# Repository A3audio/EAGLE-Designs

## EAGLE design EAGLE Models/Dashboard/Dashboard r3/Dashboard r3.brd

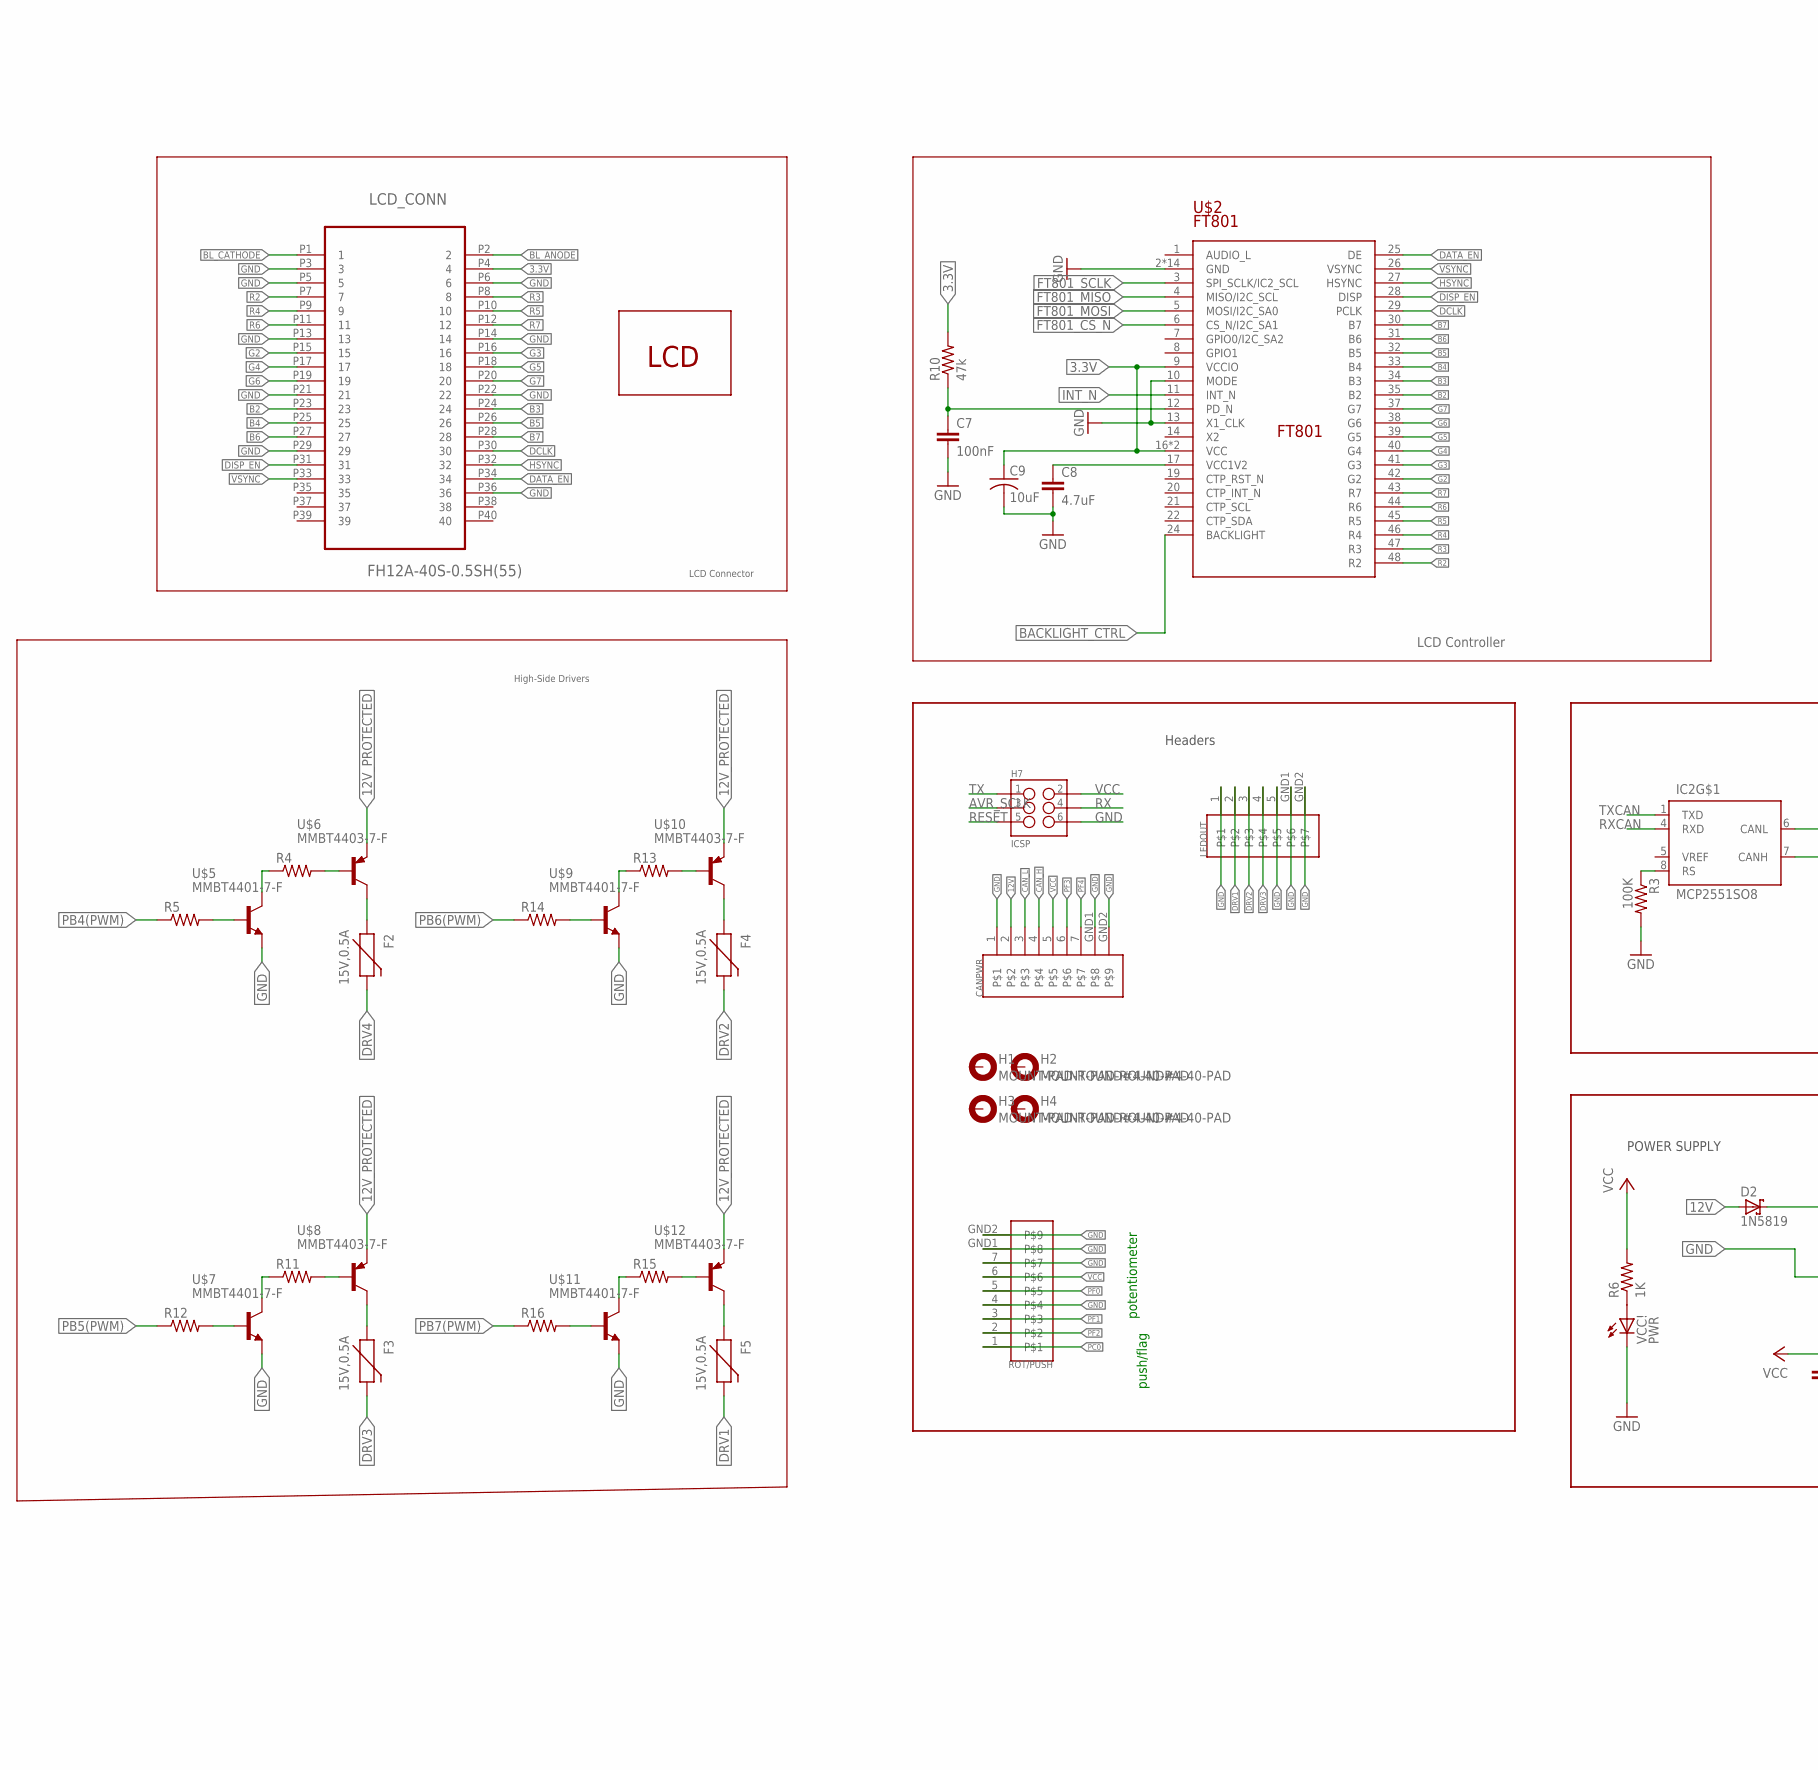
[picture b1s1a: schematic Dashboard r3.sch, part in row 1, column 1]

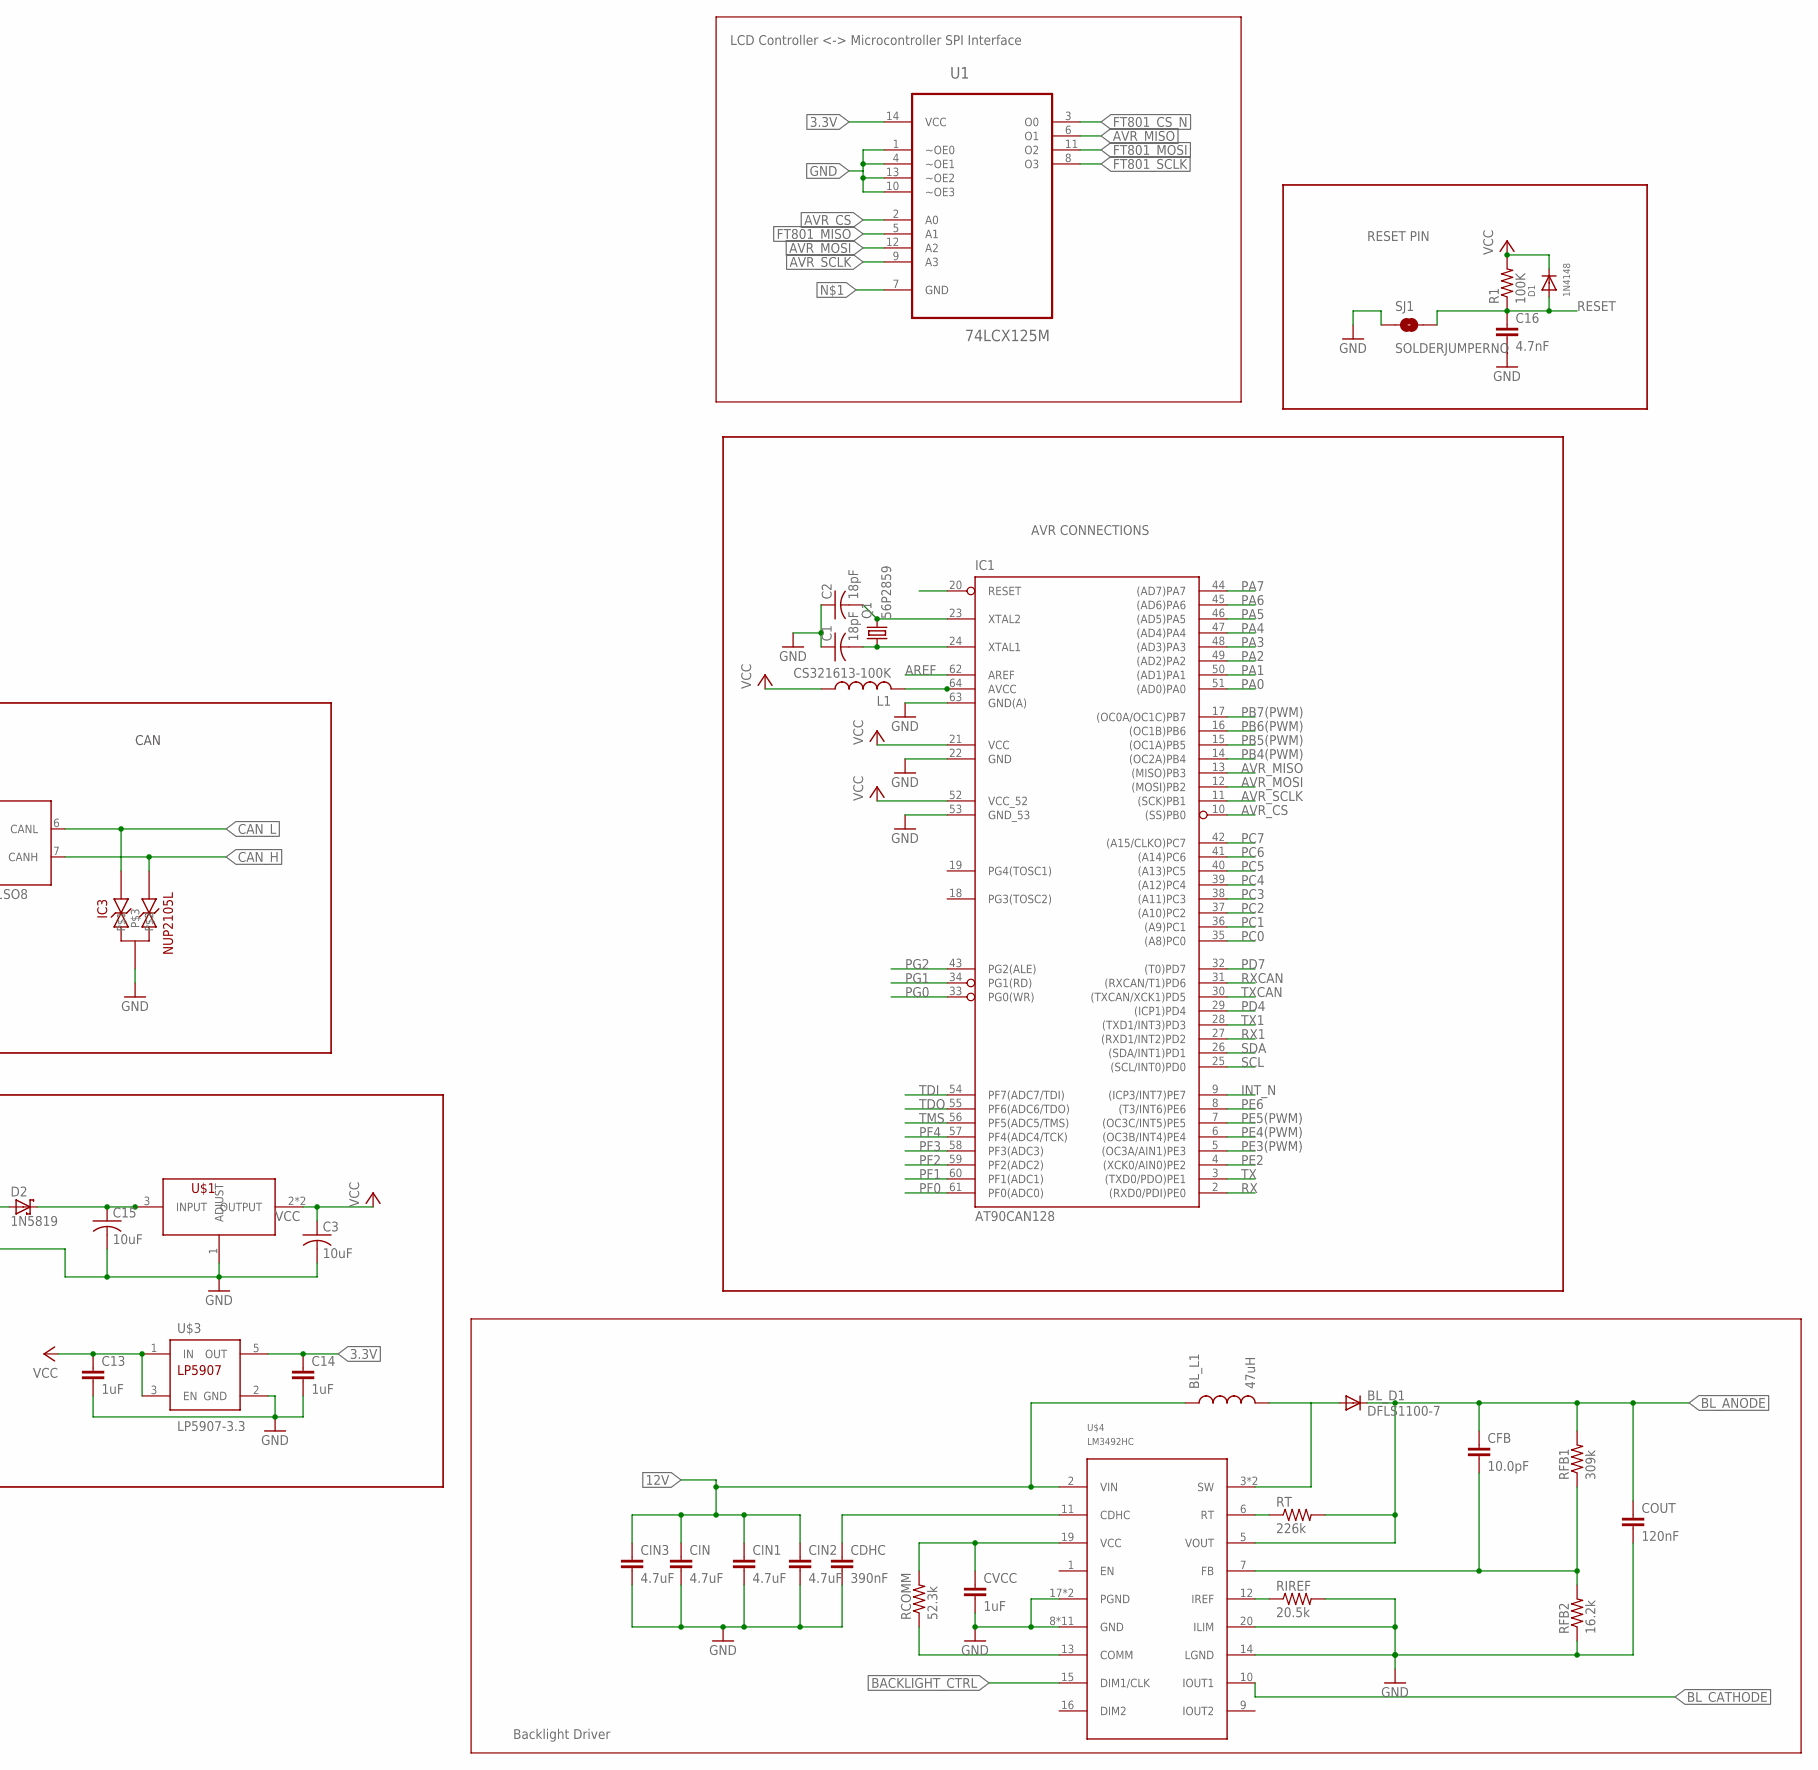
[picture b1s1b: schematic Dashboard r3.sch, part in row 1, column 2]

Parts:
BL_D1: DFLS1100-7; POWERDI-123
BL_L1: 47uH; 2-SMD
C1, C2: 18pF; C0805
C3, C9, C15: 10uF; C2220
C7: 100nF; 0603-CAP
C8: 4.7uF; 0805
C13, C14: 1uF; 0603-CAP
C16: 4.7nF; 0805
CANPWR: 53261-0771
CDHC: 390nF; 0603-CAP
CFB: 10.0pF; 0603-CAP
CIN, CIN1, CIN2, CIN3: 4.7uF; 0805
COUT: 120nF; 0805
CVCC: 1uF; 0603-CAP
D1: 1N4148; SOD-123
D2: 1N5819; SOD123
F2, F3, F4, F5: 15V,0.5A; PTC-1206
H1, H2, H3, H4: MOUNT-PAD-ROUND#4-40-PAD; #4-40-PAD-ROUND
H7: ICSP; 2X3_SMD_FCI_54202-G30
IC1: AT90CAN128; TQFP64
IC2: MCP2551SO8; SO08
IC3: NUP2105L; SOT-23
L1: CS321613-100K; L3216C
LCD_CONN: FH12A-40S-0.5SH(55); HIROSE_FH12A-40S-0.5SH(55)
LEDOUT: 53261-0571
Q1: 56P2859; HC49UP
R1, R3: 100K; R0805
R4, R5, R11, R12, R13, R14, R15, R16: RESISTOR0603; 0603-RES
R6: 1K; R0805
R10: 47k; 0603-RES
RCOMM: 52.3k; 0603-RES
RFB1: 309k; 0603-RES
RFB2: 16.2k; 0603-RES
RIREF: 20.5k; 0603-RES
ROT/PUSH: 53261-0771
RT: 226k; 0603-RES
SJ1: SOLDERJUMPERNO; SJ_2S-NO
U1: 74LCX125M; SOIC127P600X175-14N
U$1: NCP1117; SOT-223-4
U$2: FT801; RGZ48_5P15X5P15
U$3: LP5907-3.3; SOT23-DBV
U$4: LM3492HC; PWP0020A
U$5, U$7, U$9, U$11: MMBT4401-7-F; SOT-23-3
U$6, U$8, U$10, U$12: MMBT4403-7-F; SOT-23-3
U$13: TCG043WQLBAANN-GN00; TCG043WQLBAANN
VCC!: PWR; CHIPLED_0805

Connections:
3.3V: C9.1, C14.1, LCD_CONN.P4 (4), R10.2, U1.14 (VCC), U$2.9 (VCCIO), U$2.16 (VCC), U$2.18 (VCC), U$3.5 (OUT)
12V: BL_L1.1, CANPWR.2, CIN.1, CIN1.1, CIN2.1, CIN3.1, D2.A, U$4.2 (VIN)
12V_PROTECTED: C15.1, D2.C, U$1.3 (INPUT), U$6.P$3 (E), U$8.P$3 (E), U$10.P$3 (E), U$12.P$3 (E)
AREF: IC1.62 (AREF)
AVR_CS: IC1.10 ((SS)PB0), U1.2 (A0)
AVR_MISO: IC1.13 ((MISO)PB3), U1.6 (O1)
AVR_MOSI: IC1.12 ((MOSI)PB2), U1.12 (A2)
AVR_SCLK: H7.3, IC1.11 ((SCK)PB1), U1.9 (A3)
B2: LCD_CONN.P23 (23), U$2.35 (B2)
B3: LCD_CONN.P24 (24), U$2.34 (B3)
B4: LCD_CONN.P25 (25), U$2.33 (B4)
B5: LCD_CONN.P26 (26), U$2.32 (B5)
B6: LCD_CONN.P27 (27), U$2.31 (B6)
B7: LCD_CONN.P28 (28), U$2.30 (B7)
BACKLIGHT_CTRL: U$2.24 (BACKLIGHT), U$4.15 (DIM1/CLK)
BL_ANODE: BL_D1.C, CFB.1, COUT.1, LCD_CONN.P2 (2), RFB1.2, RT.2, U$4.5 (VOUT)
BL_CATHODE: LCD_CONN.P1 (1), U$4.10 (IOUT1)
CAN_H: CANPWR.4, IC2.7 (CANH), IC3.2
CAN_L: CANPWR.3, IC2.6 (CANL), IC3.1
DATA_EN: LCD_CONN.P34 (34), U$2.25 (DE)
DCLK: LCD_CONN.P30 (30), U$2.29 (PCLK)
DISP_EN: LCD_CONN.P31 (31), U$2.28 (DISP)
DRV1: F5.2, LEDOUT.2
DRV2: F4.2, LEDOUT.3
DRV3: F3.2, LEDOUT.4
DRV4: F2.2
FT801_CS_N: U1.3 (O0), U$2.6 (CS_N/I2C_SA1)
FT801_MISO: U1.5 (A1), U$2.4 (MISO/I2C_SCL)
FT801_MOSI: U1.11 (O2), U$2.5 (MOSI/I2C_SA0)
FT801_SCLK: U1.8 (O3), U$2.3 (SPI_SCLK/IC2_SCL)
G2: LCD_CONN.P15 (15), U$2.42 (G2)
G3: LCD_CONN.P16 (16), U$2.41 (G3)
G4: LCD_CONN.P17 (17), U$2.40 (G4)
G5: LCD_CONN.P18 (18), U$2.39 (G5)
G6: LCD_CONN.P19 (19), U$2.38 (G6)
G7: LCD_CONN.P20 (20), U$2.37 (G7)
GND: C1.1, C2.1, C3.2, C7.2, C8.2, C9.2, C13.2, C14.2, C15.2, C16.2, CANPWR.1, CDHC.2, CIN.2, CIN1.2, CIN2.2, CIN3.2, COUT.2, CVCC.2, H7.6, IC1.22 (GND), IC1.53 (GND_53), IC1.63 (GND(A)), IC2.2 (GND), IC3.3, LCD_CONN.P3 (3), LCD_CONN.P5 (5), LCD_CONN.P6 (6), LCD_CONN.P13 (13), LCD_CONN.P14 (14), LCD_CONN.P21 (21), LCD_CONN.P22 (22), LCD_CONN.P29 (29), LCD_CONN.P36 (36), LEDOUT.1, LEDOUT.5, LEDOUT.GND1, LEDOUT.GND2, R3.2, RFB2.1, RIREF.2, ROT/PUSH.4, ROT/PUSH.7, ROT/PUSH.GND1, ROT/PUSH.GND2, SJ1.1, U1.1 (~OE0), U1.4 (~OE1), U1.10 (~OE3), U1.13 (~OE2), U$1.1 (ADJUST), U$2.2 (GND), U$2.10 (MODE), U$2.13 (X1_CLK), U$2.15 (GND), U$2.23 (GND), U$2.36 (GND), U$2.EP (GND), U$2.V_1 (GND), U$2.V_2 (GND), U$2.V_3 (GND), U$2.V_4 (GND), U$2.V_5 (GND), U$2.V_6 (GND), U$2.V_7 (GND), U$2.V_8 (GND), U$2.V_9 (GND), U$3.2 (GND), U$4.8 (GND), U$4.14 (LGND), U$4.17 (PGND), U$4.18 (PGND), U$4.20 (ILIM), U$4.EP (GND), U$4.P$1 (GND), U$4.P$2 (GND), U$4.P$3 (GND), U$4.P$4 (GND), U$4.P$5 (GND), U$4.P$6 (GND), U$4.P$7 (GND), U$4.P$8 (GND), U$4.P$9 (GND), U$5.P$3 (E), U$7.P$3 (E), U$9.P$3 (E), U$11.P$3 (E), VCC!.C
HSYNC: LCD_CONN.P32 (32), U$2.27 (HSYNC)
INT_N: IC1.9 ((ICP3/INT7)PE7), U$2.11 (INT_N)
unnamed: C8.1, U$2.17 (VCC1V2)
unnamed: C7.1, R10.1, U$2.12 (PD_N)
unnamed: CVCC.1, RCOMM.2, U$4.19 (VCC)
unnamed: RCOMM.1, U$4.13 (COMM)
unnamed: IC2.8 (RS), R3.1
unnamed: CDHC.1, U$4.11 (CDHC)
unnamed: BL_D1.A, BL_L1.2, U$4.3 (SW), U$4.4 (SW)
unnamed: R6.1, VCC!.A
unnamed: CFB.2, RFB1.1, RFB2.2, U$4.7 (FB)
unnamed: C1.2, IC1.24 (XTAL1), Q1.1
unnamed: RT.1, U$4.6 (RT)
unnamed: RIREF.1, U$4.12 (IREF)
unnamed: IC1.64 (AVCC), L1.2
unnamed: R5.2, U$5.P$2 (B)
unnamed: R4.2, U$6.P$2 (B)
unnamed: R4.1, U$5.P$1 (C)
unnamed: F2.1, U$6.P$1 (C)
unnamed: R12.2, U$7.P$2 (B)
unnamed: R11.2, U$8.P$2 (B)
unnamed: R11.1, U$7.P$1 (C)
unnamed: F3.1, U$8.P$1 (C)
unnamed: R14.2, U$9.P$2 (B)
unnamed: R13.2, U$10.P$2 (B)
unnamed: R13.1, U$9.P$1 (C)
unnamed: F4.1, U$10.P$1 (C)
unnamed: R16.2, U$11.P$2 (B)
unnamed: R15.2, U$12.P$2 (B)
unnamed: R15.1, U$11.P$1 (C)
unnamed: F5.1, U$12.P$1 (C)
PA0: IC1.51 ((AD0)PA0)
PA1: IC1.50 ((AD1)PA1)
PA2: IC1.49 ((AD2)PA2)
PA3: IC1.48 ((AD3)PA3)
PA4: IC1.47 ((AD4)PA4)
PA5: IC1.46 ((AD5)PA5)
PA6: IC1.45 ((AD6)PA6)
PA7: IC1.44 ((AD7)PA7)
PB4(PWM): IC1.14 ((OC2A)PB4), R5.1
PB5(PWM): IC1.15 ((OC1A)PB5), R12.1
PB6(PWM): IC1.16 ((OC1B)PB6), R14.1
PB7(PWM): IC1.17 ((OC0A/OC1C)PB7), R16.1
PC0: IC1.35 ((A8)PC0), ROT/PUSH.1
PC1: IC1.36 ((A9)PC1)
PC2: IC1.37 ((A10)PC2)
PC3: IC1.38 ((A11)PC3)
PC4: IC1.39 ((A12)PC4)
PC5: IC1.40 ((A13)PC5)
PC6: IC1.41 ((A14)PC6)
PC7: IC1.42 ((A15/CLKO)PC7)
PD4: IC1.29 ((ICP1)PD4)
PD7: IC1.32 ((T0)PD7)
PE2: IC1.4 ((XCK0/AIN0)PE2)
PE3(PWM): IC1.5 ((OC3A/AIN1)PE3)
PE4(PWM): IC1.6 ((OC3B/INT4)PE4)
PE5(PWM): IC1.7 ((OC3C/INT5)PE5)
PE6: IC1.8 ((T3/INT6)PE6)
PF0: IC1.61 (PF0(ADC0)), ROT/PUSH.5
PF1: IC1.60 (PF1(ADC1)), ROT/PUSH.3
PF2: IC1.59 (PF2(ADC2)), ROT/PUSH.2
PF3: CANPWR.6, IC1.58 (PF3(ADC3))
PF4: CANPWR.7, IC1.57 (PF4(ADC4/TCK))
PG0: IC1.33 (PG0(WR))
PG1: IC1.34 (PG1(RD))
PG2: IC1.43 (PG2(ALE))
R2: LCD_CONN.P7 (7), U$2.48 (R2)
R3: LCD_CONN.P8 (8), U$2.47 (R3)
R4: LCD_CONN.P9 (9), U$2.46 (R4)
R5: LCD_CONN.P10 (10), U$2.45 (R5)
R6: LCD_CONN.P11 (11), U$2.44 (R6)
R7: LCD_CONN.P12 (12), U$2.43 (R7)
RESET: C16.1, D1.A, H7.5, IC1.20 (RESET), R1.1, SJ1.2
RX: H7.4, IC1.2 ((RXD0/PDI)PE0)
RX1: IC1.27 ((RXD1/INT2)PD2)
RXCAN: IC1.31 ((RXCAN/T1)PD6), IC2.4 (RXD)
SCL: IC1.25 ((SCL/INT0)PD0)
SDA: IC1.26 ((SDA/INT1)PD1)
TDI: IC1.54 (PF7(ADC7/TDI))
TDO: IC1.55 (PF6(ADC6/TDO))
TMS: IC1.56 (PF5(ADC5/TMS))
TX: H7.1, IC1.3 ((TXD0/PDO)PE1)
TX1: IC1.28 ((TXD1/INT3)PD3)
TXCAN: IC1.30 ((TXCAN/XCK1)PD5), IC2.1 (TXD)
VCC: C3.1, C13.1, CANPWR.5, D1.C, H7.2, IC1.21 (VCC), IC1.52 (VCC_52), IC2.3 (VCC), L1.1, R1.2, R6.2, ROT/PUSH.6, U$1.2 (OUTPUT), U$1.4 (OUTPUT), U$3.1 (IN), U$3.3 (EN)
VSYNC: LCD_CONN.P33 (33), U$2.26 (VSYNC)
XTAL1: C2.2, IC1.23 (XTAL2), Q1.2

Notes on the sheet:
POWER SUPPLY
CAN
RESET PIN
AVR CONNECTIONS
Headers
LCD Controller
LCD Controller <-> Microcontroller SPI Interface
Backlight Driver
LCD Connector
High-Side Drivers
potentiometer
push/flag

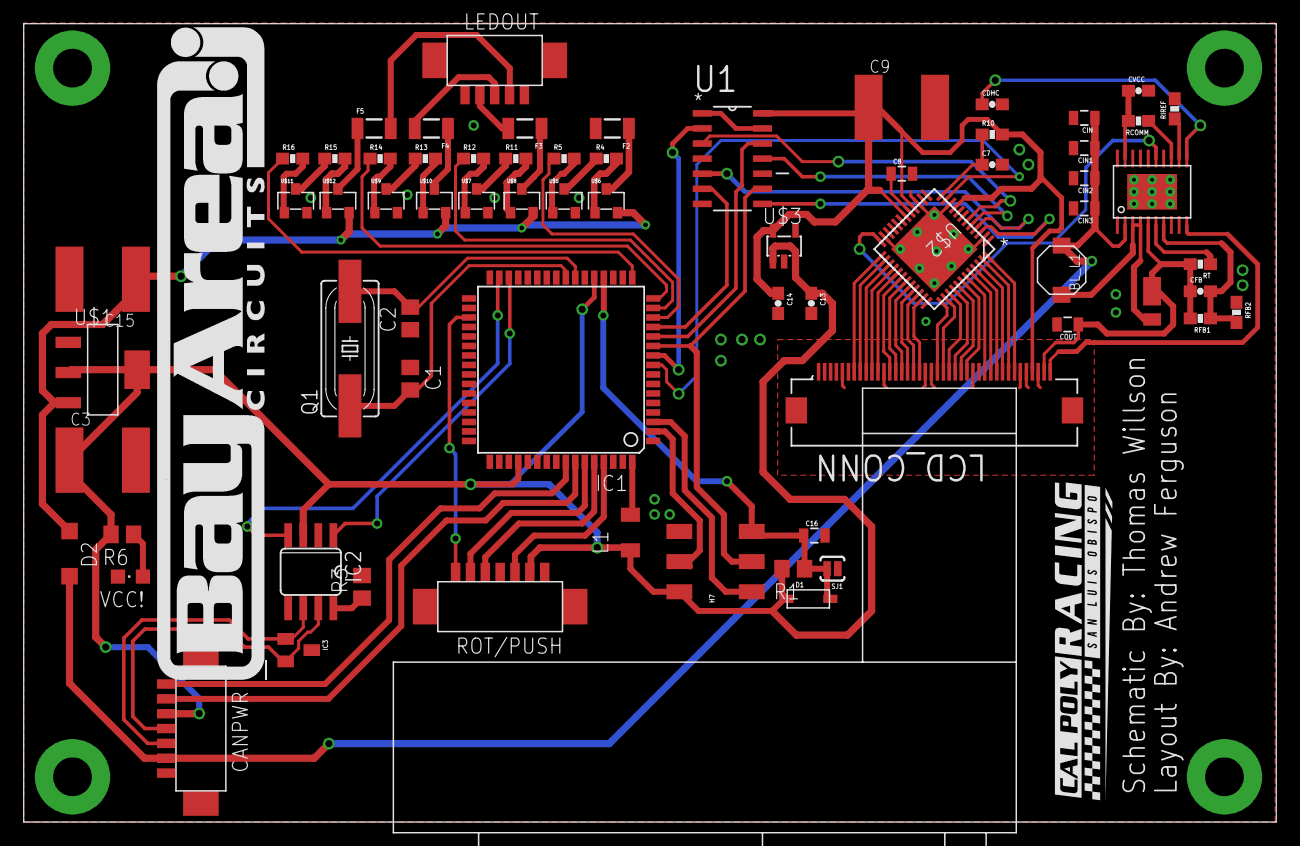
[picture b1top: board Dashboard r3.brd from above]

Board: 2 copper layers, 105.5 x 67.2 mm, 73 parts (0 on the bottom side), 90 nets.

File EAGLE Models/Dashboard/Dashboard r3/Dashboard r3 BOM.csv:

"Part";"Value";"Device";"Package";"Description";"MPN";"OC_FARNELL";"OC_NEWARK";"PACKAGE";"SUPPLIER";
"BL_D1";"DFLS1100-7";"DFLS1100-7";"POWERDI-123";"";"";"";"";"";"";
"BL_L1";"47uH";"LTF4022-D";"2-SMD";"LTF4022";"";"";"";"";"";
"C1";"18pF";"C-USC0805";"C0805";"CAPACITOR, American symbol";"";"";"";"";"";
"C2";"18pF";"C-USC0805";"C0805";"CAPACITOR, American symbol";"";"";"";"";"";
"C3";"10uF";"C-USC2220";"C2220";"CAPACITOR, American symbol";"";"";"";"";"";
"C7";"100nF";"CAP0603-CAP";"0603-CAP";"Capacitor";"";"";"";"";"";
"C8";"4.7uF";"CAP0805";"0805";"Capacitor";"";"";"";"";"";
"C9";"10uF";"C-USC2220";"C2220";"CAPACITOR, American symbol";"";"";"";"";"";
"C13";"1uF";"CAP0603-CAP";"0603-CAP";"Capacitor";"";"";"";"";"";
"C14";"1uF";"CAP0603-CAP";"0603-CAP";"Capacitor";"";"";"";"";"";
"C15";"10uF";"C-USC2220";"C2220";"CAPACITOR, American symbol";"";"";"";"";"";
"C16";"4.7nF";"CAP0805";"0805";"Capacitor";"";"";"";"";"";
"CANPWR";"";"53261-0771";"53261-0771";"";"";"";"";"";"";
"CDHC";"390nF";"CAP0603-CAP";"0603-CAP";"Capacitor";"";"";"";"";"";
"CFB";"10.0pF";"CAP0603-CAP";"0603-CAP";"Capacitor";"";"";"";"";"";
"CIN";"4.7uF";"CAP0805";"0805";"Capacitor";"";"";"";"";"";
"CIN1";"4.7uF";"CAP0805";"0805";"Capacitor";"";"";"";"";"";
"CIN2";"4.7uF";"CAP0805";"0805";"Capacitor";"";"";"";"";"";
"CIN3";"4.7uF";"CAP0805";"0805";"Capacitor";"";"";"";"";"";
"COUT";"120nF";"CAP0805";"0805";"Capacitor";"";"";"";"";"";
"CVCC";"1uF";"CAP0603-CAP";"0603-CAP";"Capacitor";"";"";"";"";"";
"D1";"1N4148";"DIODESOD-123";"SOD-123";"Diode";"";"";"";"";"";
"D2";"1N5819";"1N5819-BSOD123";"SOD123";"1.0A SCHOTTKY BARRIER RECTIFIER";"";"";"";"";"";
"F2";"15V,0.5A";"PTCSMD";"PTC-1206";"Resettable Fuse PTC";"";"";"";"";"";
"F3";"15V,0.5A";"PTCSMD";"PTC-1206";"Resettable Fuse PTC";"";"";"";"";"";
"F4";"15V,0.5A";"PTCSMD";"PTC-1206";"Resettable Fuse PTC";"";"";"";"";"";
"F5";"15V,0.5A";"PTCSMD";"PTC-1206";"Resettable Fuse PTC";"";"";"";"";"";
"H1";"MOUNT-PAD-ROUND#4-40-PAD";"MOUNT-PAD-ROUND#4-40-PAD";"#4-40-PAD-ROUND";"MOUNTING PAD, round";"";"";"";"";"";
"H2";"MOUNT-PAD-ROUND#4-40-PAD";"MOUNT-PAD-ROUND#4-40-PAD";"#4-40-PAD-ROUND";"MOUNTING PAD, round";"";"";"";"";"";
"H3";"MOUNT-PAD-ROUND#4-40-PAD";"MOUNT-PAD-ROUND#4-40-PAD";"#4-40-PAD-ROUND";"MOUNTING PAD, round";"";"";"";"";"";
"H4";"MOUNT-PAD-ROUND#4-40-PAD";"MOUNT-PAD-ROUND#4-40-PAD";"#4-40-PAD-ROUND";"MOUNTING PAD, round";"";"";"";"";"";
"H7";"ICSP";"M03X2SMD_FCI";"2X3_SMD_FCI_54202-G30";"2x3 .1" header.";"";"";"";"";"";
"IC1";"AT90CAN128";"AT90CAN128";"TQFP64";"";"";"";"";"";"";
"IC2";"MCP2551SO8";"MCP2551SO8";"SO08";"CAN Tranceiver Microchip";"";"";"";"";"";
"IC3";"NUP2105L";"NUP2105L";"SOT-23";"";"";"";"";"";"";
"L1";"CS321613-100K";"L-USL3216C";"L3216C";"INDUCTOR, American symbol";"";"";"";"";"";
"LCD_CONN";"FH12A-40S-0.5SH(55)";"FH12A-40S-0.5SH(55)";"HIROSE_FH12A-40S-0.5SH(55)";"SOCKET FFC/FPC, ZIF, 0.5MM, 40WAY";"FH12A-40S-0.5SH(55)";"1324569";"34M6194";"SOCKET FFC/FPC, ZIF, 0.5MM, 40WAY";"Hirose";
"LEDOUT";"";"53261-0571";"53261-0571";"";"";"";"";"";"";
"Q1";"56P2859";"CRYSTALSMD";"HC49UP";"Various standard crystals. Proven footprints. Spark Fun Electronics SKU : COM-00534";"";"";"";"";"";
"R1";"100K";"R-US_R0805";"R0805";"RESISTOR, American symbol";"";"";"";"";"";
"R3";"100K";"R-US_R0805";"R0805";"RESISTOR, American symbol";"";"";"";"";"";
"R4";"";"RESISTOR0603";"0603-RES";"Resistor";"";"";"";"";"";
"R5";"";"RESISTOR0603";"0603-RES";"Resistor";"";"";"";"";"";
"R6";"1K";"R-US_R0805";"R0805";"RESISTOR, American symbol";"";"";"";"";"";
"R10";"47k";"RESISTOR0603";"0603-RES";"Resistor";"";"";"";"";"";
"R11";"";"RESISTOR0603";"0603-RES";"Resistor";"";"";"";"";"";
"R12";"";"RESISTOR0603";"0603-RES";"Resistor";"";"";"";"";"";
"R13";"";"RESISTOR0603";"0603-RES";"Resistor";"";"";"";"";"";
"R14";"";"RESISTOR0603";"0603-RES";"Resistor";"";"";"";"";"";
"R15";"";"RESISTOR0603";"0603-RES";"Resistor";"";"";"";"";"";
"R16";"";"RESISTOR0603";"0603-RES";"Resistor";"";"";"";"";"";
"RCOMM";"52.3k";"RESISTOR0603";"0603-RES";"Resistor";"";"";"";"";"";
"RFB1";"309k";"RESISTOR0603-RES";"0603-RES";"Resistor";"";"";"";"";"";
"RFB2";"16.2k";"RESISTOR0603-RES";"0603-RES";"Resistor";"";"";"";"";"";
"RIREF";"20.5k";"RESISTOR0603-RES";"0603-RES";"Resistor";"";"";"";"";"";
"ROT/PUSH";"";"53261-0771";"53261-0771";"";"";"";"";"";"";
"RT";"226k";"RESISTOR0603-RES";"0603-RES";"Resistor";"";"";"";"";"";
"SJ1";"SOLDERJUMPERNO";"SOLDERJUMPERNO";"SJ_2S-NO";"Solder Jumper";"";"";"";"";"";
"U$1";"NCP1117";"NCP1117";"SOT-223-4";"";"";"";"";"";"";
"U$2";"FT801";"FT801";"RGZ48_5P15X5P15";"IC TFT LCD CONTROLLER 48VQFN";"";"";"";"";"";
"U$3";"LP5907-3.3";"LP5907";"SOT23-DBV";"";"";"";"";"";"";
"U$4";"LM3492HC";"LM3492HC";"PWP0020A";"";"";"";"";"";"";
"U$5";"MMBT4401-7-F";"MMBT4401-7-F";"SOT-23-3";"";"";"";"";"";"";
"U$6";"MMBT4403-7-F";"MMBT4403-7-F";"SOT-23-3";"";"";"";"";"";"";
"U$7";"MMBT4401-7-F";"MMBT4401-7-F";"SOT-23-3";"";"";"";"";"";"";
"U$8";"MMBT4403-7-F";"MMBT4403-7-F";"SOT-23-3";"";"";"";"";"";"";
"U$9";"MMBT4401-7-F";"MMBT4401-7-F";"SOT-23-3";"";"";"";"";"";"";
"U$10";"MMBT4403-7-F";"MMBT4403-7-F";"SOT-23-3";"";"";"";"";"";"";
"U$11";"MMBT4401-7-F";"MMBT4401-7-F";"SOT-23-3";"";"";"";"";"";"";
"U$12";"MMBT4403-7-F";"MMBT4403-7-F";"SOT-23-3";"";"";"";"";"";"";
"U$13";"TCG043WQLBAANN-GN00";"TCG043WQLBAANN-GN00";"TCG043WQLBAANN";"";"";"";"";"";"";
"U1";"74LCX125M";"74LCX125M";"SOIC127P600X175-14N";"Low Voltage Quad Buffer with 5V Tolerant Inputs and Outputs";"74LCX125M";"1013776";"78K6286";"SOIC-14";"Fairchild";
"VCC!";"PWR";"LEDCHIPLED_0805";"CHIPLED_0805";"LED";"";"";"";"";"";

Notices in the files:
parts and their libraries:
SparkFun-Capacitors: Licensing: CC v3.0 Share-Alike You are welcome to use this library for commercial purposes.
